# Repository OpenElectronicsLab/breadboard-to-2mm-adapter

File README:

# breadboard-to-2mm-adapter

This is an adapter board to plug allow 2mm headers to easily
plug into a breadboard.

This project is in early development and is not yet ready for use.

License
-------
CERN Open Hardware Licence, version 1.2 or later.
See LICENSE.txt for details.

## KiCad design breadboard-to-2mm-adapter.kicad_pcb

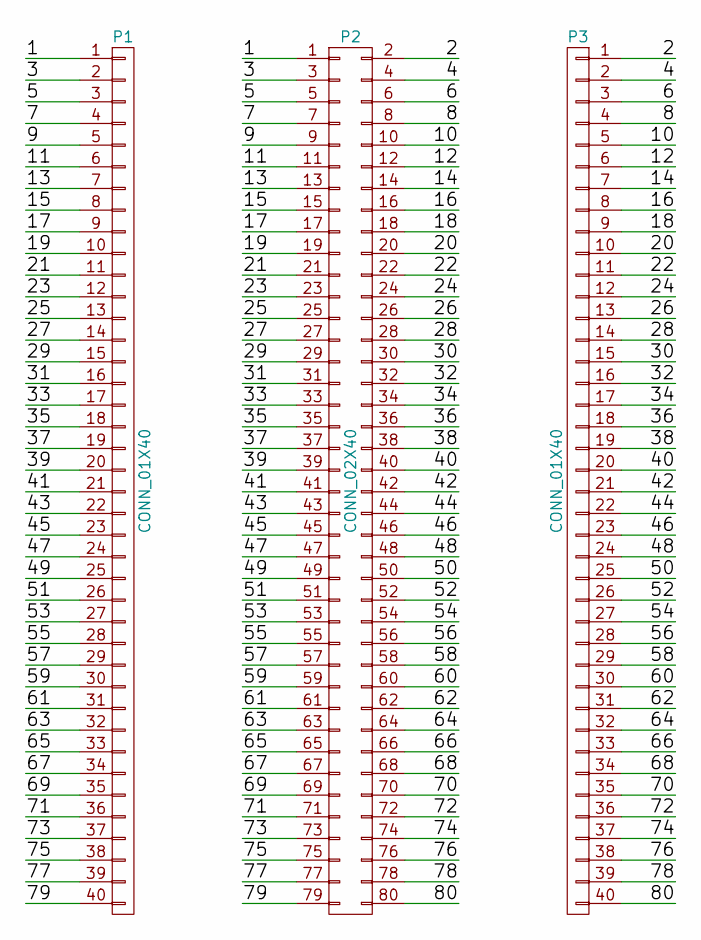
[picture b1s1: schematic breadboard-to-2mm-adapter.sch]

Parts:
P1, P3: CONN_01X40; Pin_Header_Straight_1x40
P2: CONN_02X40

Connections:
/3: P1.2, P2.3
/4: P2.4, P3.2
/5: P1.3, P2.5
/6: P2.6, P3.3
/7: P1.4, P2.7
/8: P2.8, P3.4
/9: P1.5, P2.9
/10: P2.10, P3.5
/11: P1.6, P2.11
/12: P2.12, P3.6
/13: P1.7, P2.13
/14: P2.14, P3.7
/15: P1.8, P2.15
/16: P2.16, P3.8
/17: P1.9, P2.17
/18: P2.18, P3.9
/19: P1.10, P2.19
/20: P2.20, P3.10
/21: P1.11, P2.21
/22: P2.22, P3.11
/23: P1.12, P2.23
/24: P2.24, P3.12
/25: P1.13, P2.25
/26: P2.26, P3.13
/27: P1.14, P2.27
/28: P2.28, P3.14
/29: P1.15, P2.29
/30: P2.30, P3.15
/31: P1.16, P2.31
/32: P2.32, P3.16
/33: P1.17, P2.33
/34: P2.34, P3.17
/35: P1.18, P2.35
/36: P2.36, P3.18
/37: P1.19, P2.37
/38: P2.38, P3.19
/39: P1.20, P2.39
/40: P2.40, P3.20
/41: P1.21, P2.41
/42: P2.42, P3.21
/43: P1.22, P2.43
/44: P2.44, P3.22
/45: P1.23, P2.45
/46: P2.46, P3.23
/47: P1.24, P2.47
/48: P2.48, P3.24
/49: P1.25, P2.49
/50: P2.50, P3.25
/51: P1.26, P2.51
/52: P2.52, P3.26
/53: P1.27, P2.53
/54: P2.54, P3.27
/55: P1.28, P2.55
/56: P2.56, P3.28
/57: P1.29, P2.57
/58: P2.58, P3.29
/59: P1.30, P2.59
/60: P2.60, P3.30
/61: P1.31, P2.61
/62: P2.62, P3.31
/63: P1.32, P2.63
/64: P2.64, P3.32
/65: P1.33, P2.65
/66: P2.66, P3.33
/67: P1.34, P2.67
/68: P2.68, P3.34
/69: P1.35, P2.69
/70: P2.70, P3.35
/71: P1.36, P2.71
/72: P2.72, P3.36
/73: P1.37, P2.73
/74: P2.74, P3.37
/75: P1.38, P2.75
/76: P2.76, P3.38
/77: P1.39, P2.77
/78: P2.78, P3.39
/79: P1.40, P2.79
/80: P2.80, P3.40
GND: P1.1, P2.1
VCC: P2.2, P3.1

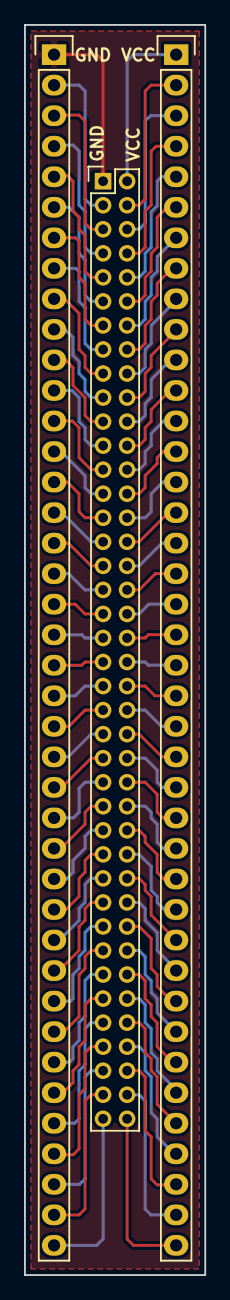
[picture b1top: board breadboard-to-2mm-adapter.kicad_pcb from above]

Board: 4 copper layers, 15.0 x 104.0 mm, 3 parts (0 on the bottom side), 80 nets.

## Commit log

2016-02-21 init
2016-02-21 CERN OHL v1.2+
2016-02-21 export the 2x40 2.54mm pitch to start with
2016-02-21 convert to 2mm
2016-02-21 move to Pin_Headers_2mm.pretty/
2016-02-21 gitignore
2016-02-21 kicad project
2016-02-21 initial pcb 2x40
2016-02-21 need to verify pad and drill values
2016-02-21 TODO: noise review, also
2016-02-21 add 2x40 to names
2016-02-21 Add hirose datasheet URL
2016-02-21 add a 2x20 adapter
